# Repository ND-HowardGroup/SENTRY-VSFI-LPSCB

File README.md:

# SENTRY-VSFI-LPSCB
Schematics and PCB Design for GPS and LoRa enabled low-power sensor communications board (LPSCB).

Developed as part of the [DHS SENTRY Center of Excellence](https://sentry.northeastern.edu/), these boards
and prototype development boards for integrating GPS, LoRa, and I2C connected sensors. This is the first generation
device for preliminary testing and education purposes.

These boards can be programmed over USB as if they are a Raspberry Pi Pico 1 (RP2040) following Raspberry Pi's
[standard documentation](https://www.raspberrypi.com/documentation/microcontrollers/pico-series.html).

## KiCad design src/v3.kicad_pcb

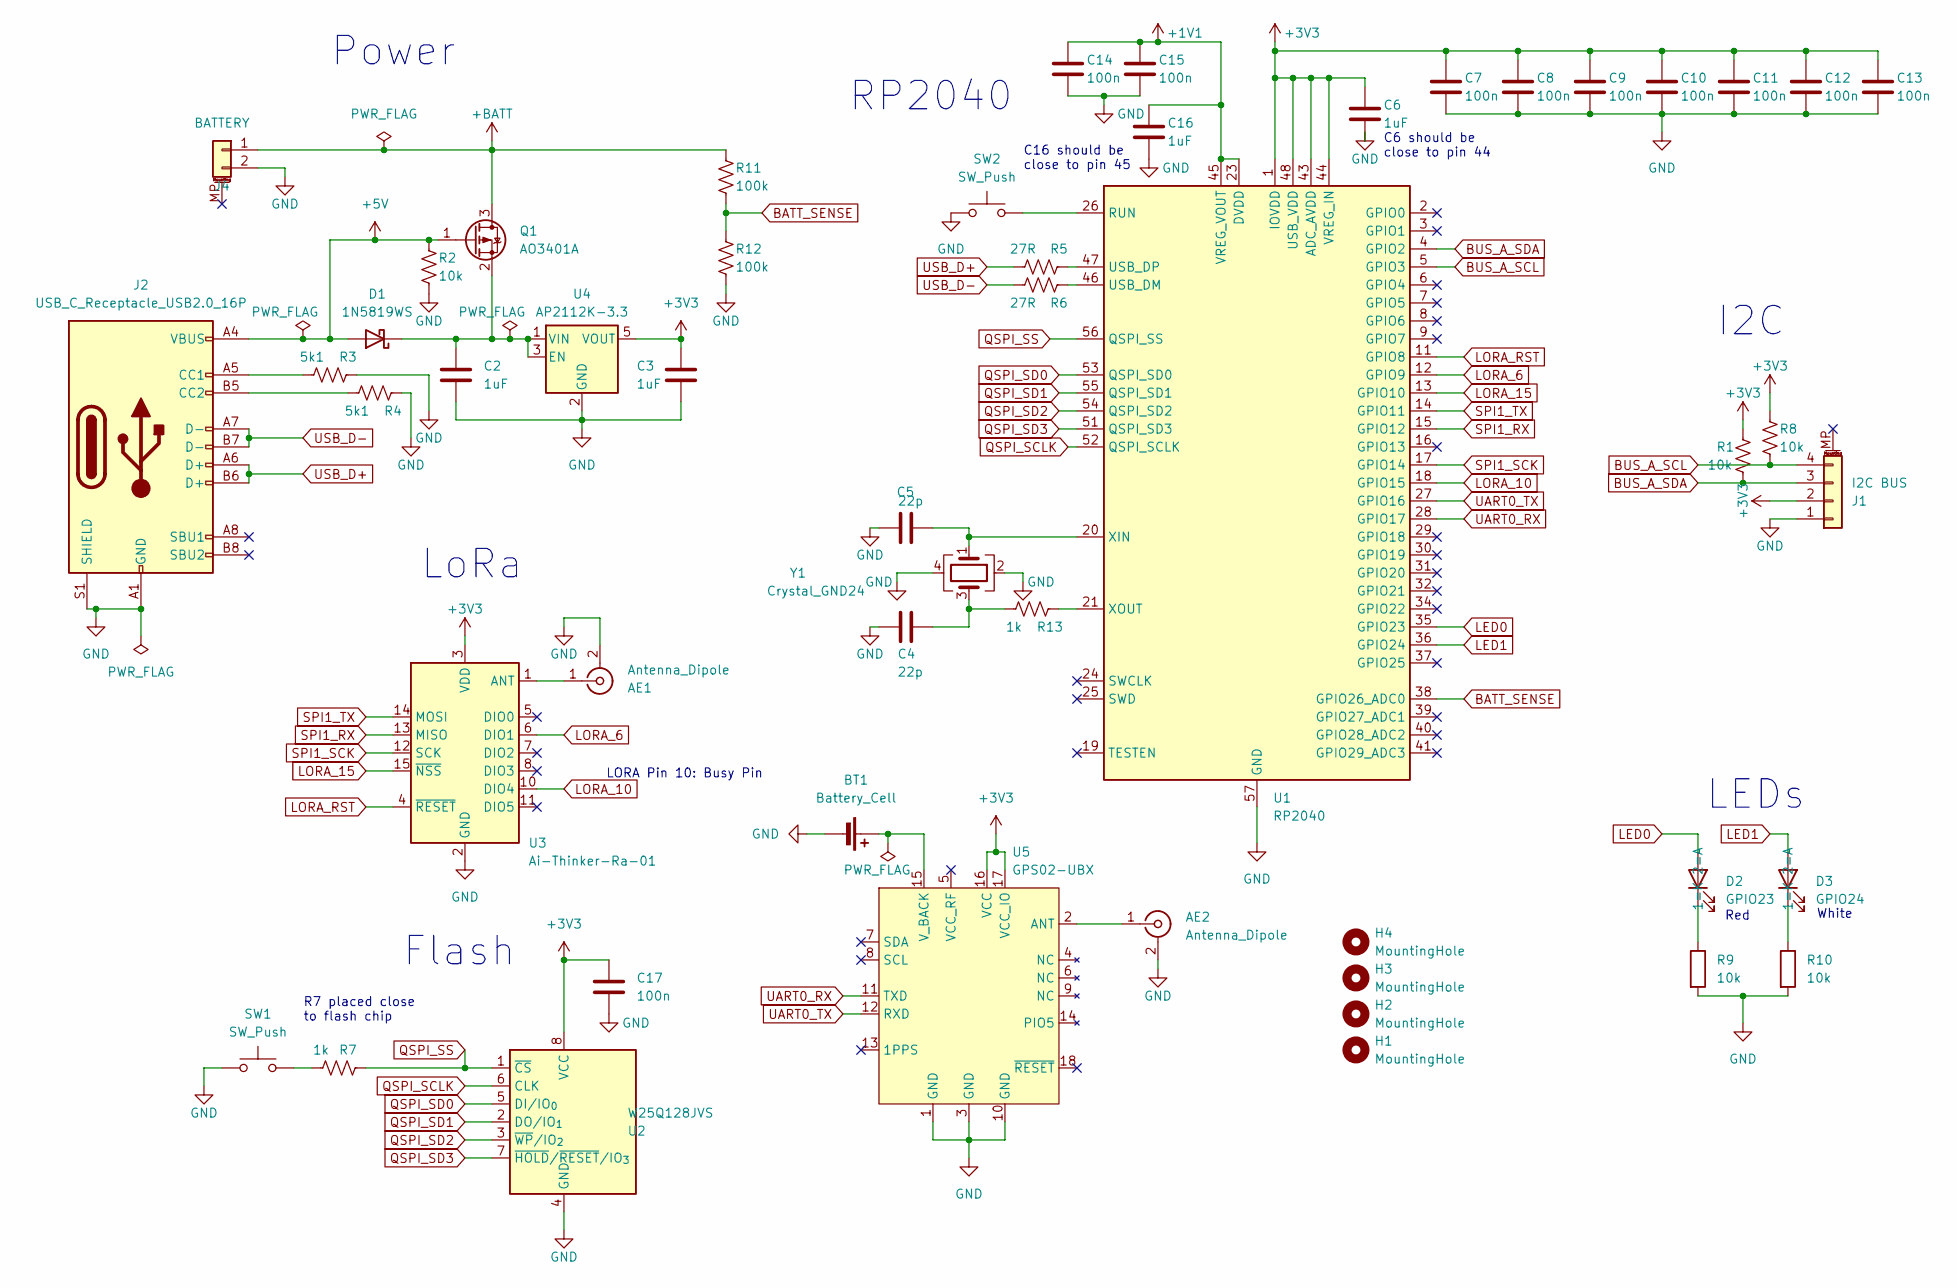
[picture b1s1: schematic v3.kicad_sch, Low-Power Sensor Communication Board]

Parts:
AE1, AE2: Antenna_Dipole; U.FL_Hirose_U.FL-R-SMT-1_Vertical; LCSC C88374
BT1: Battery_Cell; BatteryHolder_Multicomp_BC-2001_1x2032; LCSC C964829
C2, C3, C6, C16: 1uF; C_0402_1005Metric; LCSC C52923
C4, C5: 22p; C_0402_1005Metric; LCSC C1555
C7, C8, C9, C10, C11, C12, C13, C14, C15, C17: 100n; C_0402_1005Metric; LCSC C1525
D1: 1N5819WS; D_SOD-323; LCSC C191023
D2: GPIO23; LED_0603_1608Metric; LCSC C2286
D3: GPIO24; LED_0603_1608Metric; LCSC C2290
H1, H2, H3, H4: MountingHole; MountingHole_3.2mm_M3
J1: I2C BUS; JST_SH_BM04B-SRSS-TB_1x04-1MP_P1.00mm_Vertical; LCSC C160390
J2: USB_C_Receptacle_USB2.0_16P; USB_C_Receptacle_HCTL_HC-TYPE-C-16P-01A; LCSC C2894897
J4: BATTERY; JST_PH_S2B-PH-SM4-TB_1x02-1MP_P2.00mm_Horizontal; LCSC C295747
Q1: AO3401A; SOT-23; LCSC C15127
R1, R2, R8, R9, R10: 10k; R_0402_1005Metric; LCSC C25744
R3, R4: 5k1; R_0402_1005Metric; LCSC C25905
R5, R6: 27R; R_0402_1005Metric; LCSC C25100
R7, R13: 1k; R_0402_1005Metric; LCSC C11702
R11, R12: 100k; R_0402_1005Metric; LCSC C25741
SW1, SW2: SW_Push; SW_SPST_SKQG_WithStem; LCSC C318884
U1: RP2040; QFN-56-1EP_7x7mm_P0.4mm_EP3.2x3.2mm; LCSC C2040
U2: W25Q128JVS; SOIC-8_5.3x5.3mm_P1.27mm; LCSC C97521
U3: Ai-Thinker-Ra-01; Ai-Thinker-Ra-01-LoRa; LCSC C2764087
U4: AP2112K-3.3; SOT-23-5; LCSC C51118
U5: GPS02-UBX; QFN-20_14.5x16.45_Pitch1.8mm; LCSC C5356636
Y1: Crystal_GND24; Crystal_SMD_3225-4Pin_3.2x2.5mm; LCSC C9002

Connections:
+1V1: C14.1, C15.1, C16.1, U1.23 (DVDD), U1.45 (VREG_VOUT), U1.50 (DVDD)
+3V3: C3.1, C6.1, C7.1, C8.1, C9.1, C10.1, C11.1, C12.1, C13.1, C17.1, J1.2, R1.1, R8.1, U1.1 (IOVDD), U1.10 (IOVDD), U1.22 (IOVDD), U1.33 (IOVDD), U1.42 (IOVDD), U1.43 (ADC_AVDD), U1.44 (VREG_IN), U1.48 (USB_VDD), U1.49 (IOVDD), U2.8 (VCC), U3.3 (VDD), U4.5 (VOUT), U5.16 (VCC), U5.17 (VCC_IO)
+5V: D1.2 (A), J2.A4 (VBUS), J2.A9 (VBUS), J2.B4 (VBUS), J2.B9 (VBUS), Q1.1 (G), R2.1
+BATT: J4.1, Q1.3 (D), R11.1
BATT_SENSE: R11.2, R12.1, U1.38 (GPIO26_ADC0)
BUS_A_SCL: J1.4, R8.2, U1.5 (GPIO3)
BUS_A_SDA: J1.3, R1.2, U1.4 (GPIO2)
GND: AE1.2 (Ext), AE2.2 (Ext), BT1.2 (-), C2.2, C3.2, C4.2, C5.1, C6.2, C7.2, C8.2, C9.2, C10.2, C11.2, C12.2, C13.2, C14.2, C15.2, C16.2, C17.2, J1.1, J2.A1 (GND), J2.A12 (GND), J2.B1 (GND), J2.B12 (GND), J2.S1 (SHIELD), J4.2, R2.2, R3.1, R4.2, R9.2, R10.2, R12.2, SW1.1, SW2.1, U1.57 (GND), U2.4 (GND), U3.2 (GND), U3.9 (GND), U3.16 (GND), U4.2 (GND), U5.1 (GND), U5.3 (GND), U5.10 (GND), Y1.2, Y1.4
LED0: D2.2 (A), U1.35 (GPIO23)
LED1: D3.2 (A), U1.36 (GPIO24)
LORA_6: U1.12 (GPIO9), U3.6 (DIO1)
LORA_10: U1.18 (GPIO15), U3.10 (DIO4)
LORA_15: U1.13 (GPIO10), U3.15 (~NSS)
LORA_RST: U1.11 (GPIO8), U3.4 (~RESET)
unnamed: AE1.1 (In), U3.1 (ANT)
unnamed: AE2.1 (In), U5.2 (ANT)
unnamed: BT1.1 (+), U5.15 (V_BACK)
unnamed: C4.1, R13.2, Y1.3
unnamed: C2.1, D1.1 (K), Q1.2 (S), U4.1 (VIN), U4.3 (EN)
unnamed: D2.1 (K), R9.1
unnamed: D3.1 (K), R10.1
unnamed: J2.A5 (CC1), R3.2
unnamed: J2.B5 (CC2), R4.1
unnamed: R7.1, SW1.2
unnamed: SW2.2, U1.26 (RUN)
unnamed: R6.1, U1.46 (USB_DM)
unnamed: R5.1, U1.47 (USB_DP)
unnamed: C5.2, U1.20 (XIN), Y1.1
unnamed: R13.1, U1.21 (XOUT)
QSPI_SCLK: U1.52 (QSPI_SCLK), U2.6 (CLK)
QSPI_SD0: U1.53 (QSPI_SD0), U2.5 (DI/IO_{0})
QSPI_SD1: U1.55 (QSPI_SD1), U2.2 (DO/IO_{1})
QSPI_SD2: U1.54 (QSPI_SD2), U2.3 (~WP/IO_{2})
QSPI_SD3: U1.51 (QSPI_SD3), U2.7 (~HOLD/~RESET/IO_{3})
QSPI_SS: R7.2, U1.56 (QSPI_SS), U2.1 (~CS)
SPI1_RX: U1.15 (GPIO12), U3.13 (MISO)
SPI1_SCK: U1.17 (GPIO14), U3.12 (SCK)
SPI1_TX: U1.14 (GPIO11), U3.14 (MOSI)
UART0_RX: U1.28 (GPIO17), U5.11 (TXD)
UART0_TX: U1.27 (GPIO16), U5.12 (RXD)
USB_D+: J2.A6 (D+), J2.B6 (D+), R5.2
USB_D-: J2.A7 (D-), J2.B7 (D-), R6.2

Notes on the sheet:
I2C
R7 placed close to flash chip
LORA Pin 10: Busy Pin
RP2040
C6 should be close to pin 44
C16 should be close to pin 45
LEDs
White
Power
Red
LoRa
Flash

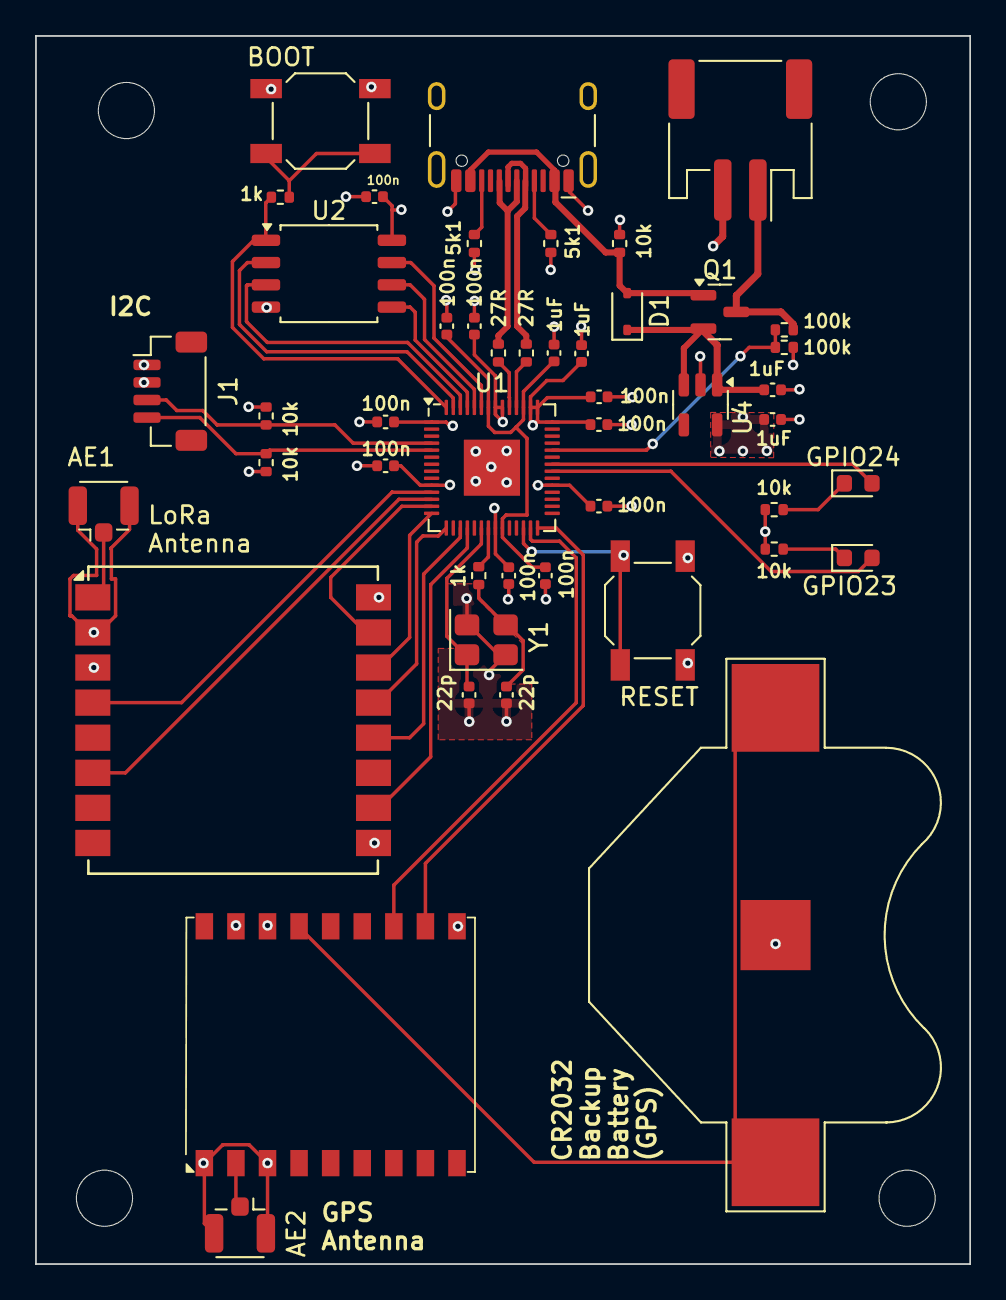
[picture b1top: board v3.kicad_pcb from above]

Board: 4 copper layers, 53.3 x 70.0 mm, 51 parts (0 on the bottom side), 42 nets.

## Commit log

2025-11-14 Initial upload
